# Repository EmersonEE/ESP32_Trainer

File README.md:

# ESP32 Trainer
Proyecto de Electrónica Aplicada 1 - **USAC**

# 📘 Temario del Proyecto

- 🔹 [Introducción](#-introducción)
- 🔹 [ESP32 Trainer](#-esp32-trainer)
- 🔹 [ESP32 Trainer Pinout](#esp32-trainer-pinout)
- 🔹 [Materiales](#-materiales)
- 🔹 [Diseño PCB - KiCad](#-diseño-pcb---kicad)
- 🔹 [Proyectos Demostrativos](#-proyectos-demostrativos)
<!-- - 🎥 [Video de Funcionamiento](#video-de-funcionamiento) -->

---

## 🧩 Introducción

En el ámbito del diseño electrónico y el desarrollo de prototipos, existe una necesidad creciente de contar con herramientas integradas que simplifiquen el proceso de aprendizaje, experimentación y construcción de soluciones funcionales. Las placas de desarrollo convencionales suelen requerir múltiples módulos adicionales para realizar proyectos completos, lo que incrementa la complejidad, los costos y el tiempo de implementación.

Este proyecto propone el diseño y fabricación de una **placa entrenadora basada en el [ESP32-WROOM-32](https://www.espressif.com/sites/default/files/documentation/esp32-wroom-32_datasheet_en.pdf)**, orientada a estudiantes, makers y profesionales. Su objetivo es integrar en una sola plataforma los elementos esenciales para trabajar con entradas/salidas digitales y analógicas, comunicación serial, control de cargas de alto voltaje, y más.

Entre sus características destacan:

- 🔘 Botones, LEDs y potenciómetros integrados para pruebas rápidas.
- ⚡ Control de cargas de 110V/220V mediante relés.
- 🔌 Interfaces UART, I2C y SPI disponibles desde headers.
- 📦 Diseño compacto y profesional en PCB de doble capa.

Con esta solución, se busca facilitar el desarrollo de proyectos de electrónica y automatización, reduciendo la necesidad de hardware adicional y mejorando la experiencia de aprendizaje.

[🔙 Volver al Temario](#-temario-del-proyecto)

## 🔌 ESP32 Trainer

[🔙 Volver al Temario](#-temario-del-proyecto)

## ESP32 Trainer Pinout

[Ver en PDF](pinout_esp32.pdf)

[🔙 Volver al Temario](#-temario-del-proyecto)

## 🧰 Materiales  

En esta sección se detallan todos los componentes electrónicos utilizados para el ensamblaje de la placa entrenadora basada en el ESP32-WROOM-32. La tabla incluye el identificador de cada componente, la cantidad necesaria, su valor o referencia, y el modelo de huella utilizado en el diseño PCB con KiCad.

<details><summary><b>Lista de Materiales  - BOM</b></summary>

| 🧾 Componente | 🔢 Cantidad | 💡 Valor       | 📐 Huella (KiCad)                                          |
|--------------|-------------|----------------|-------------------------------------------------------------|
| BZ1          | 1           | Buzzer         | Buzzer_12x9.5RM7.6                                          |
| C1, C2       | 2           | 22pF           | C_1206_3216Metric_Pad1.33x1.80mm_HandSolder                 |
| C10, C12     | 2           | 100uF          | CP_Elec_5x5.4                                               |
| C11, C13, C5, C6, C9 | 5   | 100nF          | C_1206_3216Metric_Pad1.33x1.80mm_HandSolder                 |
| C14–C16, C3–C4, C7–C8 | 7 | 0.1uF          | C_1206_3216Metric_Pad1.33x1.80mm_HandSolder                 |
| D1, D10, D7  | 3           | LED Verde      | LED_1210_3225Metric_Pad1.42x2.65mm_HandSolder               |
| D11, D13, D9 | 3           | SS24           | D_SMA                                                       |
| D12, D3, D8  | 3           | LED Azul       | LED_1210_3225Metric_Pad1.42x2.65mm_HandSolder               |
| D14–D16      | 3           | WS2812B        | LED_WS2812B_PLCC4_5.0x5.0mm_P3.2mm                          |
| D2           | 1           | LED Amarillo   | LED_1210_3225Metric_Pad1.42x2.65mm_HandSolder               |
| D4–D6        | 3           | LED Rojo       | LED_1210_3225Metric_Pad1.42x2.65mm_HandSolder               |
| J1           | 1           | USB B          | USB_B_Lumberg_2411_02_Horizontal                            |
| J10, J9      | 2           | —              | PinHeader_1x03_P2.54mm_Vertical                             |
| J2           | 1           | GPIO           | PinHeader_2x04_P2.54mm_Vertical                             |
| J3           | 1           | OLED           | PinSocket_1x04_P2.54mm_Vertical                             |
| J4           | 1           | —              | PinHeader_1x04_P2.54mm_Vertical                             |
| J5           | 1           | —              | PinHeader_2x03_P2.54mm_Vertical                             |
| J6–J8        | 3           | —              | TerminalBlock_Phoenix_MKDS-1,5-3-5.08_1x03_P5.08mm_Horizontal |
| K1–K3        | 3           | —              | Relay_SPDT_SANYOU_SRD_Series_Form_C                         |
| Q1–Q6        | 6           | MMBT3904       | SOT-23                                                      |
| R1, R2, R7, R9, R11, R12 | 6 | 10K         | R_1206_3216Metric_Pad1.30x1.75mm_HandSolder                 |
| R8, R10, R13–R16, R19–R21, R24 | 10 | 470   | R_1206_3216Metric_Pad1.30x1.75mm_HandSolder                 |
| R17, R22–R23, R25 | 4      | 2.2K           | R_1206_3216Metric_Pad1.30x1.75mm_HandSolder                 |
| R18          | 1           | 4.7K           | R_1206_3216Metric_Pad1.30x1.75mm_HandSolder                 |
| R26          | 1           | 220            | R_1206_3216Metric_Pad1.30x1.75mm_HandSolder                 |
| R3, R4       | 2           | 2K             | R_1206_3216Metric_Pad1.30x1.75mm_HandSolder                 |
| R5, R6       | 2           | 1K             | R_1206_3216Metric_Pad1.30x1.75mm_HandSolder                 |
| RV1, RV2     | 2           | 100K Pot       | Potentiometer_Bourns_3296W_Vertical                         |
| SW1, SW2     | 2           | —              | SW_Tactile_SPST_NO_Straight_CK_PTS636Sx25SMTRLFS            |
| SW3, SW4     | 2           | —              | SW_PUSH_6mm                                                 |
| U1           | 1           | ESP32-WROOM-32 | ESP32-WROOM-32                                              |
| U2           | 1           | CH340G         | SOIC-16_3.9x9.9mm_P1.27mm                                   |
| U3           | 1           | AMS1117-3.3    | SOT-223-3_TabPin2                                           |
| U4–U6        | 3           | PC817          | DIP-4_W7.62mm                                               |
| Y1           | 1           | 12MHz          | Crystal_HC49-4H_Vertical                                    |
</details>

[🔙 Volver al Temario](#-temario-del-proyecto)

## 🖨️ Diseño PCB - KiCad

 [KiCad](https://www.kicad.org/) se utilizó para el diseño de la placa entrenadora basada en el ESP32-WROOM-32, permitiendo crear el esquemático del circuito, asignar huellas adecuadas a los componentes y generar el diseño del PCB en múltiples capas. Gracias a sus herramientas de visualización y comprobación de reglas, fue posible optimizar el diseño para su posterior fabricación con alta precisión.

<details><summary><b>📏 Esquemático KiCad</b></summary>

Esquemático diseñado en Kicad, se puede visualizar de forma completa en este enlace [Esquemático](Schematic.pdf)
<div align="center" >
  <p style="text-align:center;"><strong>Power Supply</strong></p>
  
</div>

<div align="center" >
  <p style="text-align:center;"><strong>USB To TTL</strong></p>
  
</div>

<div align="center" >
  <p style="text-align:center;"><strong>Boot Settings</strong></p>
  
</div>

<div align="center" >
  <p style="text-align:center;"><strong>INPUT - OUTPUT Digital</strong></p>
  
</div>

<div align="center" >
  <p style="text-align:center;"><strong>ESP32-WROOM</strong></p>
  
</div>

<div align="center" >
  <p style="text-align:center;"><strong>Analog INPUT</strong></p>
  
</div>

<div align="center" >
  <p style="text-align:center;"><strong>LED WS2812B</strong></p>
  
</div>

<div align="center" >
  <p style="text-align:center;"><strong>Buzzer</strong></p>
  
</div>

<div align="center" >
  <p style="text-align:center;"><strong>Jumper Selector</strong></p>
  
</div>

<div align="center" >
  <p style="text-align:center;"><strong>GPIO - UART</strong></p>
  
</div>

<div align="center" >
  <p style="text-align:center;"><strong>OLED I2C</strong></p>
  
</div>

<div align="center" >
  <p style="text-align:center;"><strong>Rele</strong></p>
  
</div>

</details>

<details><summary><b>🔌 Diseño del PCB </b></summary>

Diseño de la PCB en dos caras, se puede descargar los archivos para su modificación o su estudio en aca [Descargar archivos del  PCB](https://github.com/EmersonEE/ESP32_Trainer/releases/tag/untagged-a26e2b24809520548798)

<div align="center" >
  <p style="text-align:center;"><strong>Diseño 3D</strong></p>
  
</div>

<div align="center" >
  <p style="text-align:center;"><strong>Capa BUTTON</strong></p>
  
</div>

<div align="center" >
  <p style="text-align:center;"><strong>Capa TOP</strong></p>
  
</div>

<div align="center" >
  <p style="text-align:center;"><strong>Serigrafía</strong></p>
  
</div>

</details>

<details><summary><b>🖥️ Introducción a KiCad</b></summary>

KiCad es una suite de software libre para el diseño de circuitos electrónicos y la creación de placas de circuito impreso (PCB). Desarrollado originalmente por Jean-Pierre Charras y mantenido actualmente por la comunidad y la Fundación KiCad, es una herramienta poderosa y versátil que compite con soluciones comerciales en la industria electrónica.

[KiCad](https://www.kicad.org/) permite a los diseñadores electrónicos trabajar de forma integral en todo el flujo de desarrollo de hardware, desde la creación de esquemáticos eléctricos hasta la generación de archivos Gerber listos para fabricación. Entre sus principales características destacan:

✏️ Editor de esquemáticos intuitivo, con bibliotecas extensas de componentes.

🧩 Gestor de huellas (footprints) que vincula componentes con sus representaciones físicas en el PCB.

🖨️ Editor de PCB con reglas de diseño personalizables y soporte para múltiples capas.

📷 Visualizador 3D para inspeccionar el diseño de la placa antes de fabricarla.

🔁 Integración con herramientas externas para simulación eléctrica (SPICE) o gestión de proyectos.

Al ser de código abierto y multiplataforma (disponible en Windows, Linux y macOS), KiCad es una opción ideal tanto para estudiantes, makers, como para profesionales del diseño electrónico.

## 📺 Tutoriales KiCad

### Guía para el uso de KiCad #1

### Guía para el uso de KiCad #2

### Guía para el uso de KiCad #3

</details>

[🔙 Volver al Temario](#-temario-del-proyecto)

## 🧪 Proyectos Demostrativos

Con el objetivo de validar y demostrar la versatilidad de la placa entrenadora basada en el ESP32-WROOM-32, se desarrollaron cinco proyectos demostrativos que abarcan desde aplicaciones básicas hasta implementaciones más avanzadas. Estos proyectos fueron diseñados para cubrir distintos niveles de complejidad, permitiendo así ilustrar de manera progresiva el potencial de la placa tanto en el ámbito educativo como en entornos de prototipado profesional.

Cada proyecto está enfocado en destacar una o varias funcionalidades integradas de la placa, como el uso de salidas digitales con visualización por LEDs, entradas analógicas controladas por potenciómetros, manejo de salidas de alto voltaje mediante relés, así como el uso de interfaces de comunicación como UART, I2C.

<details><summary><b>🤖 💡 Proyecto 1 </b></summary>

## Proyecto: Control de Intensidad de LED con Clases Personalizadas

Este proyecto implementa un sistema modular en Arduino para el **control de un LED** utilizando clases personalizadas en C++.

### Características principales:

- **Clase `LED`**: Permite controlar un LED conectado a un pin digital o PWM. Soporta funciones como encendido, apagado, parpadeo y control de brillo mediante modulación por ancho de pulso (PWM).
- **Clase `PWM`**: Facilita la lectura de entradas analógicas y entrega los valores en diferentes formatos: raw, mapeado (0-255) y en voltios.
- En la función `setup()`, se configura un LED en el pin 2 en modo PWM.
- En el `loop()`, la intensidad del LED se ajusta dinámicamente según la lectura analógica del pin 32.

Este proyecto demuestra cómo estructurar el código de forma reutilizable y orientada a objetos para controlar hardware de forma más eficiente.

🔗 [Ver código del Proyecto 1](/Codigos%20Proyectos/Proyecto_1/)

</details>

<details><summary><b>🤖 💡 Proyecto 2 </b></summary>

## Proyecto: Detección de Movimiento y Control Remoto vía Telegram

Este proyecto implementa un sistema de monitoreo basado en **ESP32** que permite detectar movimiento mediante un sensor **PIR** y enviar notificaciones en tiempo real a un usuario específico a través de un bot de **Telegram**.

### Características principales:

- **Detección de movimiento**: El sensor PIR detecta presencia o movimiento en el entorno.
- **Notificación instantánea**: Cuando se detecta movimiento, el ESP32 envía un mensaje automáticamente al usuario mediante Telegram.
- **Control remoto**: El usuario puede encender o apagar un **LED** conectado al ESP32 enviando comandos personalizados al bot.
- **Interacción segura y directa**: Solo el usuario autorizado puede comunicarse con el bot para recibir alertas o enviar comandos.
- **Aplicación práctica**: Ideal para sistemas de vigilancia, alarmas domésticas o control remoto básico mediante mensajería.

🔗 [Ver código del Proyecto 2](/Codigos%20Proyectos/Proyecto_2/)

</details>

<details><summary><b>🤖 💡 Proyecto 3 </b></summary>

## Proyecto: Control de Focos con ESP32 y ESP RainMaker

Este proyecto utiliza un ESP32 para controlar tres focos a través de la plataforma **ESP RainMaker**, permitiendo el encendido y apagado mediante comandos de voz e integración con asistentes virtuales.

### Características principales:

- **Control inteligente**: Tres relés controlan los focos conectados a los pines **25**, **2** y **14**.
- **Dispositivos virtuales**: Se crean tres dispositivos en la nube:
  - `Foco Sala`
  - `Foco Comedor`
  - `Foco Cuarto`
- **Comandos de voz**: Compatible con asistentes virtuales mediante ESP RainMaker.
- **Aprovisionamiento BLE**: Permite la configuración inicial de red Wi-Fi mediante Bluetooth.
- **Callback personalizado**: Al recibir una orden desde RainMaker, el estado del relé correspondiente se actualiza.
- **Actualización OTA**: Soporte para actualizaciones de firmware a distancia.
- **Servicios integrados**:
  - Zona horaria
  - Programación de tareas
- **Indicadores y botones**:
  - LED indica conexión Wi-Fi activa.
  - Botón en el pin **0** permite:
    - Restablecer Wi-Fi (pulsación breve)
    - Restablecer de fábrica (pulsación prolongada)

Este proyecto es ideal para aplicaciones de automatización del hogar, demostrando la capacidad de la placa para integrarse con servicios en la nube y control por voz.

🔗 [Ver código del Proyecto 3](/Codigos%20Proyectos/Proyecto_3/)

</details>

<details><summary><b>🤖 💡 Proyecto 4 </b></summary>

## Proyecto: Controlador Web para LED RGB con ESP32

Gracias al módulo WiFi integrado del **ESP32**, es posible crear un controlador web altamente funcional para un **LED RGB**, eliminando la necesidad de ingresar manualmente valores RGB cada vez que se desea cambiar el color.

En lugar de eso, este proyecto propone una **interfaz web atractiva e interactiva**, que permite seleccionar colores de forma visual e intuitiva. Para ello, se utiliza la biblioteca **iro.js**, un potente selector de color en JavaScript que ofrece una experiencia de usuario dinámica y visualmente agradable.

La comunicación entre la interfaz web y el ESP32 se realiza mediante **WebSockets**, lo que permite actualizar el color en tiempo real sin necesidad de recargar la página. El **ESP32 actúa como servidor Web**, sirviendo la interfaz HTML y gestionando el servidor WebSocket para recibir los datos del color seleccionado.

Este enfoque proporciona un sistema eficiente, moderno y fácil de usar para controlar luces RGB a través de cualquier dispositivo con acceso a un navegador web.

[Manera de subir la carpeta Data al ESP32](https://randomnerdtutorials.com/esp32-vs-code-platformio-spiffs/)

🔗 [Ver código del Proyecto 4](/Codigos%20Proyectos/Proyecto_4/)

</details>

<details><summary><b>🤖 💡 Proyecto 5 </b></summary>

## Proyecto: Alerta de Proximidad con Sensor Ultrasónico, Pantalla OLED y Buzzer

Este proyecto utiliza un **sensor ultrasónico**, una **pantalla OLED SSD1306** y un **buzzer** para crear un sistema de alerta de proximidad.

### Funcionamiento:

- El **sensor ultrasónico** mide constantemente la distancia a un objeto frente a él.
- La **pantalla OLED** muestra en tiempo real la distancia detectada en centímetros.
- Cuando un objeto se acerca a una **distancia mínima predefinida**, el **buzzer** se activa como señal de advertencia sonora.
- Si el objeto se aleja nuevamente más allá del umbral, el buzzer se desactiva automáticamente.

Este sistema es útil como sistema de asistencia para estacionamiento, detección de intrusos, monitoreo de espacios reducidos, entre otros usos prácticos que requieren una alerta ante la cercanía de objetos.

🔗 [Ver código del Proyecto 5](/Codigos%20Proyectos/Proyecto_5/)

</details>

[🔙 Volver al Temario](#-temario-del-proyecto)

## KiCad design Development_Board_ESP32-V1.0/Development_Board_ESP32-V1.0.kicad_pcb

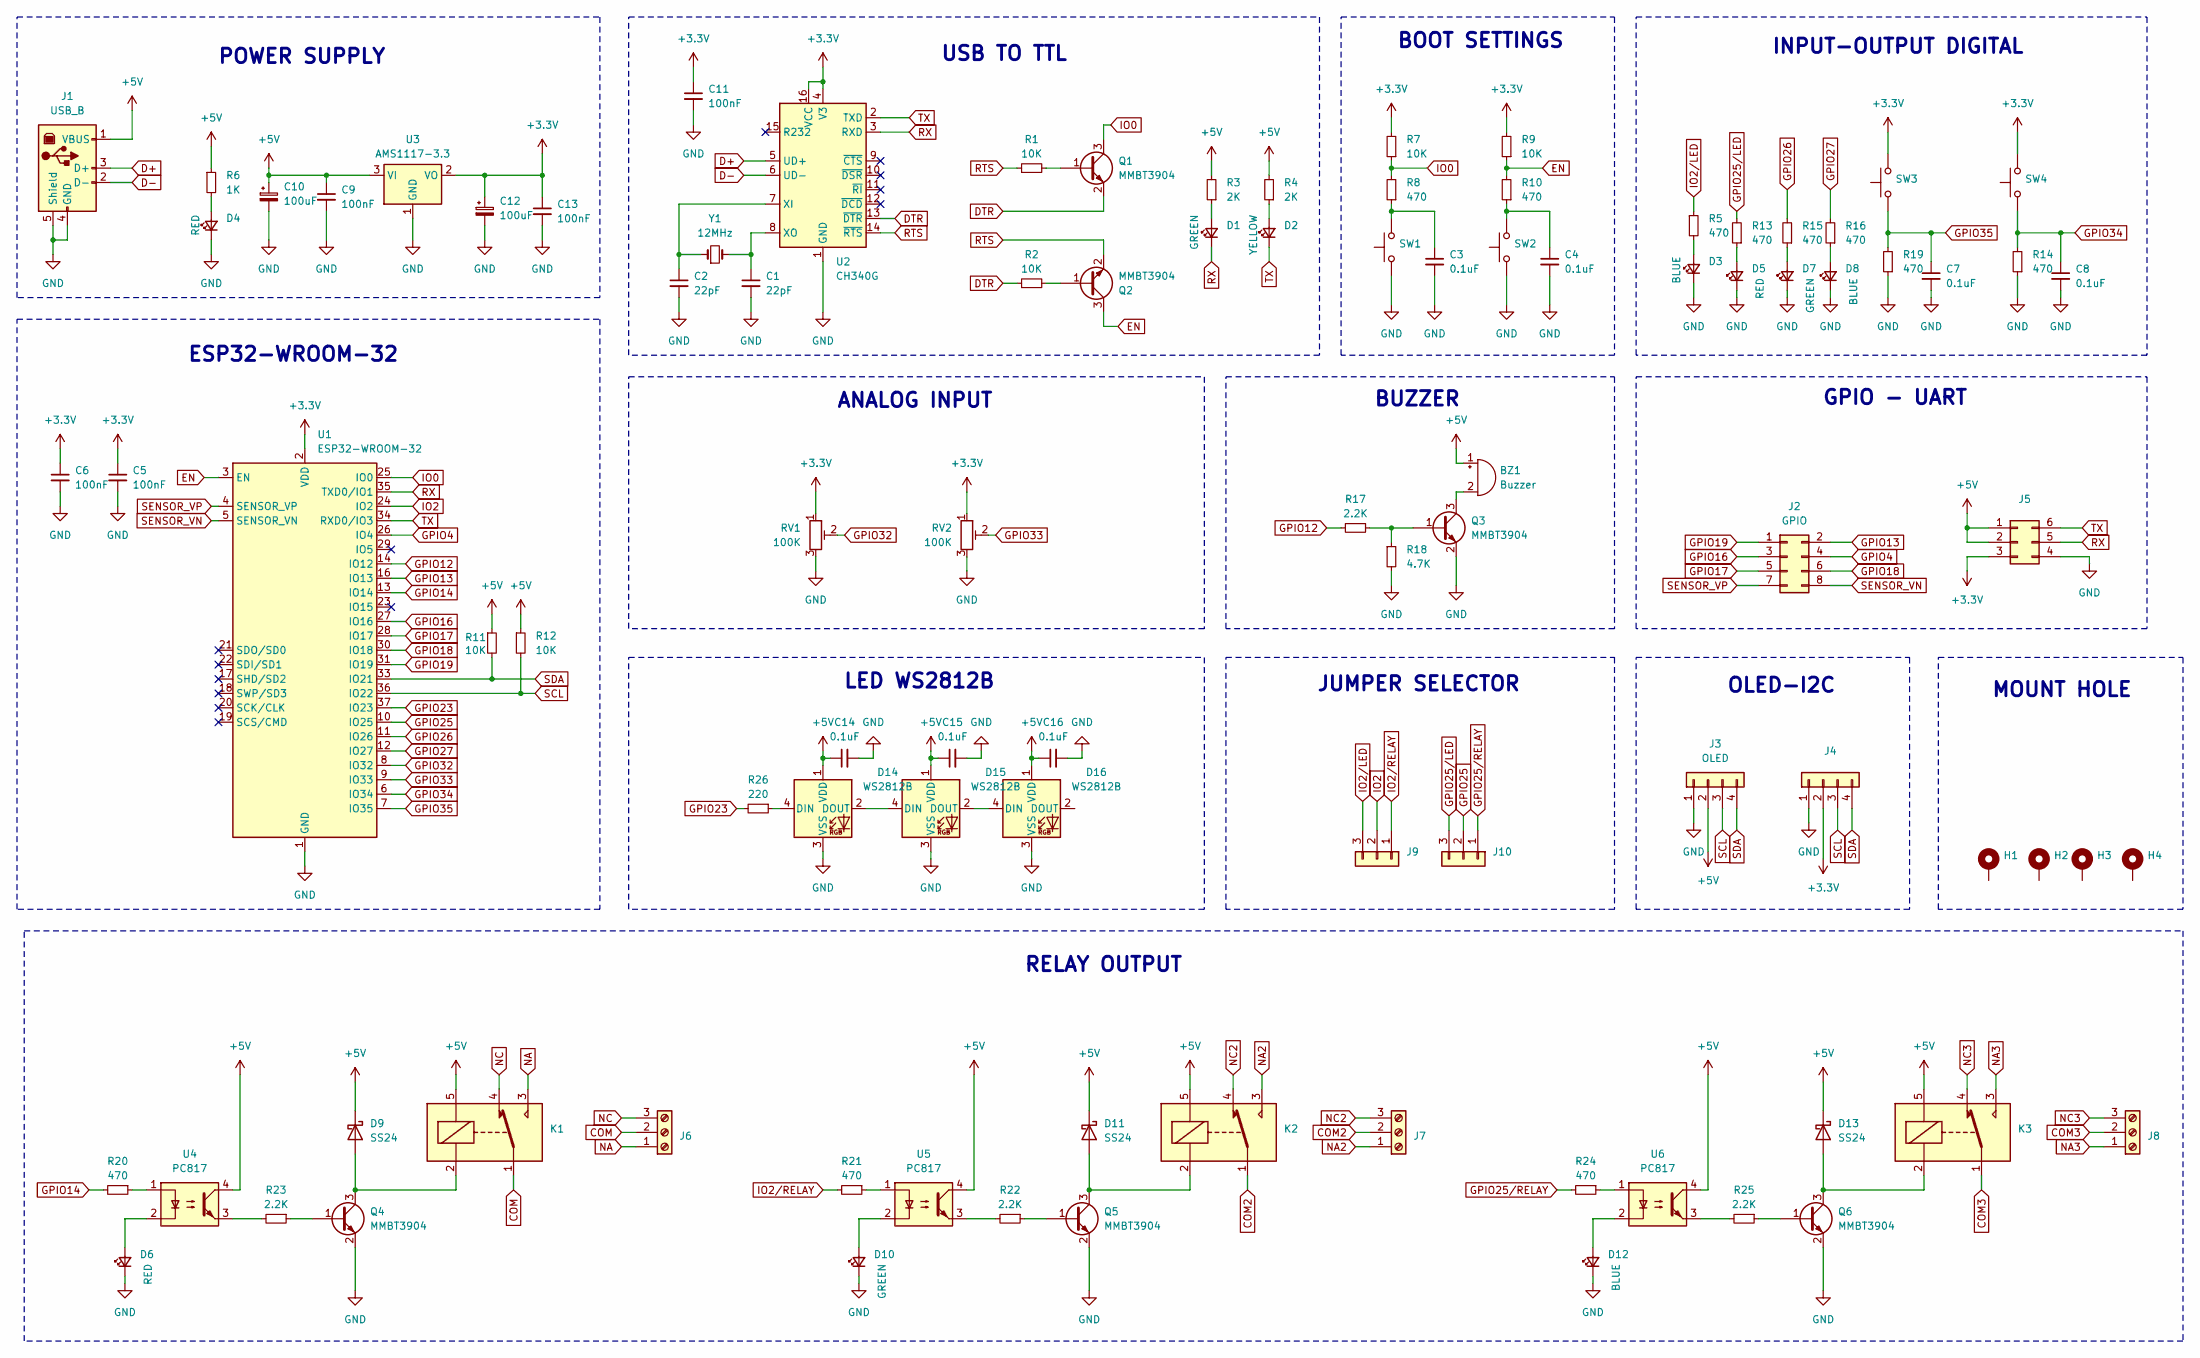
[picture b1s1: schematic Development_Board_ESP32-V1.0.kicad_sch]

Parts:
BZ1: Buzzer; Buzzer_12x9.5RM7.6
C1, C2: 22pF; C_1206_3216Metric_Pad1.33x1.80mm_HandSolder
C3, C4, C7, C8, C14, C15, C16: 0.1uF; C_1206_3216Metric_Pad1.33x1.80mm_HandSolder
C5, C6, C9, C11, C13: 100nF; C_1206_3216Metric_Pad1.33x1.80mm_HandSolder
C10, C12: 100uF; CP_Elec_5x5.4
D1, D7, D10: GREEN; LED_1210_3225Metric_Pad1.42x2.65mm_HandSolder
D2: YELLOW; LED_1210_3225Metric_Pad1.42x2.65mm_HandSolder
D3, D8, D12: BLUE; LED_1210_3225Metric_Pad1.42x2.65mm_HandSolder
D4, D5, D6: RED; LED_1210_3225Metric_Pad1.42x2.65mm_HandSolder
D9, D11, D13: SS24; D_SMA
D14, D15, D16: WS2812B; LED_WS2812B_PLCC4_5.0x5.0mm_P3.2mm
H1, H2, H3, H4: MountingHole_3.2mm_M3_Pad_Via
J1: USB_B; USB_B_Lumberg_2411_02_Horizontal
J2: GPIO; PinHeader_2x04_P2.54mm_Vertical
J3: OLED; PinSocket_1x04_P2.54mm_Vertical
J4: PinHeader_1x04_P2.54mm_Vertical
J5: PinHeader_2x03_P2.54mm_Vertical
J6, J7, J8: TerminalBlock_Phoenix_MKDS-1,5-3-5.08_1x03_P5.08mm_Horizont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
J9, J10: PinHeader_1x03_P2.54mm_Vertical
K1, K2, K3: Relay_SPDT_SANYOU_SRD_Series_Form_C
Q1, Q2, Q3, Q4, Q5, Q6: MMBT3904; SOT-23
R1, R2, R7, R9, R11, R12: 10K; R_1206_3216Metric_Pad1.30x1.75mm_HandSolder
R3, R4: 2K; R_1206_3216Metric_Pad1.30x1.75mm_HandSolder
R5, R8, R10, R13, R14, R15, R16, R19, R20, R21, R24: 470; R_1206_3216Metric_Pad1.30x1.75mm_HandSolder
R6: 1K; R_1206_3216Metric_Pad1.30x1.75mm_HandSolder
R17, R22, R23, R25: 2.2K; R_1206_3216Metric_Pad1.30x1.75mm_HandSolder
R18: 4.7K; R_1206_3216Metric_Pad1.30x1.75mm_HandSolder
R26: 220; R_1206_3216Metric_Pad1.30x1.75mm_HandSolder
RV1, RV2: 100K; Potentiometer_Bourns_3296W_Vertical
SW1, SW2: SW_Tactile_SPST_NO_Straight_CK_PTS636Sx25SMTRLFS
SW3, SW4: SW_PUSH_6mm
U1: ESP32-WROOM-32
U2: CH340G; SOIC-16_3.9x9.9mm_P1.27mm
U3: AMS1117-3.3; SOT-223-3_TabPin2
U4, U5, U6: PC817; DIP-4_W7.62mm
Y1: 12MHz; Crystal_HC49-4H_Vertical

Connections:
+3.3V: C5.1, C6.1, C11.1, C12.1, C13.1, J4.2, J5.3, R7.2, R9.2, RV1.1, RV2.1, SW3.2, SW4.2, U1.2 (VDD), U2.4 (V3), U2.16 (VCC), U3.2 (VO)
+5V: BZ1.1 (+), C9.1, C10.1, C14.1, C15.1, C16.1, D9.1 (K), D11.1 (K), D13.1 (K), D14.1 (VDD), D15.1 (VDD), D16.1 (VDD), J1.1 (VBUS), J3.2, J5.1, J5.2, K1.5, K2.5, K3.5, R3.2, R4.2, R6.1, R11.1, R12.1, U3.3 (VI), U4.4, U5.4, U6.4
COM: J6.2, K1.1
COM2: J7.2, K2.1
COM3: J8.2, K3.1
D+: J1.3 (D+), U2.5 (UD+)
D-: J1.2 (D-), U2.6 (UD-)
DTR: Q1.2 (E), R2.1, U2.13 (~DTR)
EN: Q2.3 (C), R9.1, R10.2, U1.3 (EN)
GND: C1.2, C2.2, C3.2, C4.2, C5.2, C6.2, C7.2, C8.2, C9.2, C10.2, C11.2, C12.2, C13.2, C14.2, C15.2, C16.2, D3.1 (K), D4.1 (K), D5.1 (K), D6.1 (K), D7.1 (K), D8.1 (K), D10.1 (K), D12.1 (K), D14.3 (VSS), D15.3 (VSS), D16.3 (VSS), J1.4 (GND), J1.5 (Shield), J3.1, J4.1, J5.4, Q3.2 (E), Q4.2 (E), Q5.2 (E), Q6.2 (E), R14.1, R18.2, R19.1, RV1.3, RV2.3, SW1.1, SW2.1, U1.1 (GND), U1.15 (GND), U1.38 (GND), U1.39 (GND), U2.1 (GND), U3.1 (GND)
GPIO4: J2.4, U1.26 (IO4)
GPIO12: R17.2, U1.14 (IO12)
GPIO13: J2.2, U1.16 (IO13)
GPIO14: R20.2, U1.13 (IO14)
GPIO16: J2.3, U1.27 (IO16)
GPIO17: J2.5, U1.28 (IO17)
GPIO18: J2.6, U1.30 (IO18)
GPIO19: J2.1, U1.31 (IO19)
GPIO23: R26.2, U1.37 (IO23)
GPIO25: J10.2, U1.10 (IO25)
GPIO25/LED: J10.3, R13.2
GPIO25/RELAY: J10.1, R24.2
GPIO26: R15.2, U1.11 (IO26)
GPIO27: R16.2, U1.12 (IO27)
GPIO32: RV1.2, U1.8 (IO32)
GPIO33: RV2.2, U1.9 (IO33)
GPIO34: C8.1, R14.2, SW4.1, U1.6 (IO34)
GPIO35: C7.1, R19.2, SW3.1, U1.7 (IO35)
IO0: Q1.3 (C), R7.1, R8.2, U1.25 (IO0)
IO2: J9.2, U1.24 (IO2)
IO2/LED: J9.3, R5.1
IO2/RELAY: J9.1, R21.2
NA: J6.1, K1.3
NA2: J7.1, K2.3
NA3: J8.1, K3.3
NC: J6.3, K1.4
NC2: J7.3, K2.4
NC3: J8.3, K3.4
unnamed: BZ1.2 (-), Q3.3 (C)
unnamed: C3.1, R8.1, SW1.2
unnamed: C4.1, R10.1, SW2.2
unnamed: D1.2 (A), R3.1
unnamed: D2.2 (A), R4.1
unnamed: D3.2 (A), R5.2
unnamed: D4.2 (A), R6.2
unnamed: D5.2 (A), R13.1
unnamed: D6.2 (A), U4.2
unnamed: D7.2 (A), R15.1
unnamed: D8.2 (A), R16.1
unnamed: D9.2 (A), K1.2, Q4.3 (C)
unnamed: D10.2 (A), U5.2
unnamed: D11.2 (A), K2.2, Q5.3 (C)
unnamed: D12.2 (A), U6.2
unnamed: D13.2 (A), K3.2, Q6.3 (C)
unnamed: D14.4 (DIN), R26.1
unnamed: D14.2 (DOUT), D15.4 (DIN)
unnamed: D15.2 (DOUT), D16.4 (DIN)
unnamed: Q1.1 (B), R1.2
unnamed: Q2.1 (B), R2.2
unnamed: Q3.1 (B), R17.1, R18.1
unnamed: Q4.1 (B), R23.1
unnamed: Q5.1 (B), R22.1
unnamed: Q6.1 (B), R25.1
unnamed: R20.1, U4.1
unnamed: R21.1, U5.1
unnamed: R22.2, U5.3
unnamed: R23.2, U4.3
unnamed: R24.1, U6.1
unnamed: R25.2, U6.3
unnamed: C2.1, U2.7 (XI), Y1.1
unnamed: C1.1, U2.8 (XO), Y1.2
RTS: Q2.2 (E), R1.1, U2.14 (~RTS)
RX: D1.1 (K), J5.5, U1.35 (TXD0/IO1), U2.3 (RXD)
SCL: J3.3, J4.3, R12.2, U1.36 (IO22)
SDA: J3.4, J4.4, R11.2, U1.33 (IO21)
SENSOR_VN: J2.8, U1.5 (SENSOR_VN)
SENSOR_VP: J2.7, U1.4 (SENSOR_VP)
TX: D2.1 (K), J5.6, U1.34 (RXD0/IO3), U2.2 (TXD)

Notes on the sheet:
ANALOG INPUT
BUZZER
ESP32-WROOM-32
POWER SUPPLY
LED WS2812B
MOUNT HOLE
INPUT-OUTPUT DIGITAL
BOOT SETTINGS
RELAY OUTPUT
JUMPER SELECTOR
GPIO - UART
OLED-I2C
USB TO TTL

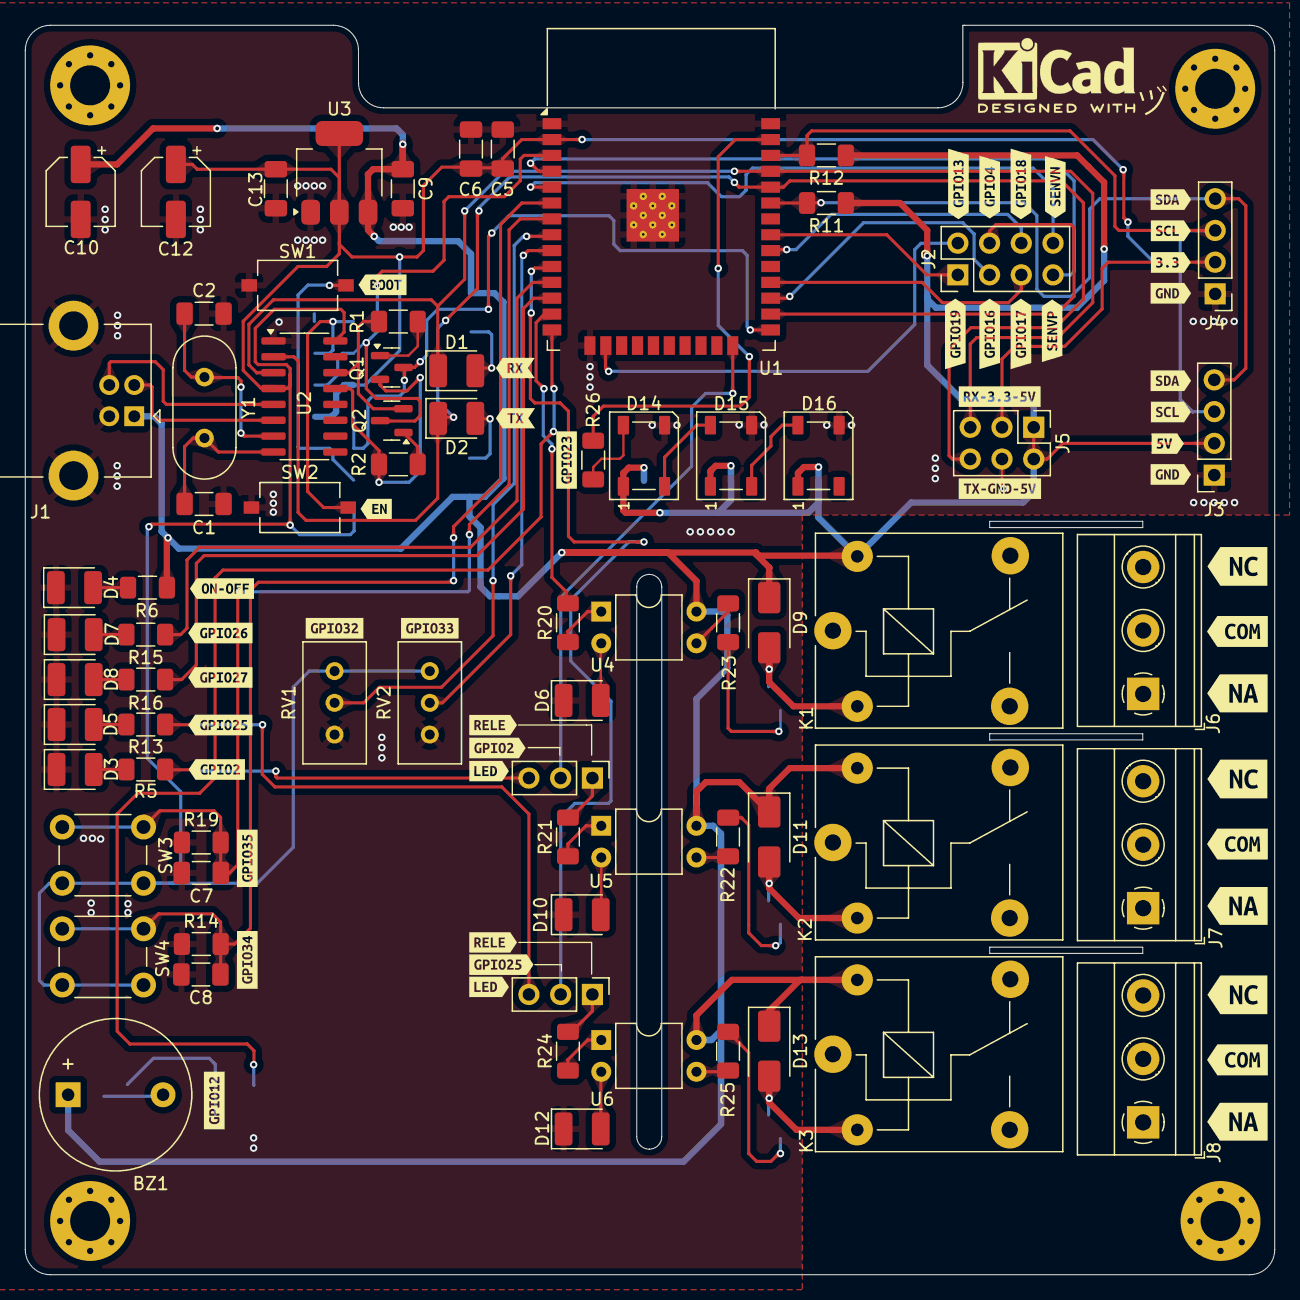
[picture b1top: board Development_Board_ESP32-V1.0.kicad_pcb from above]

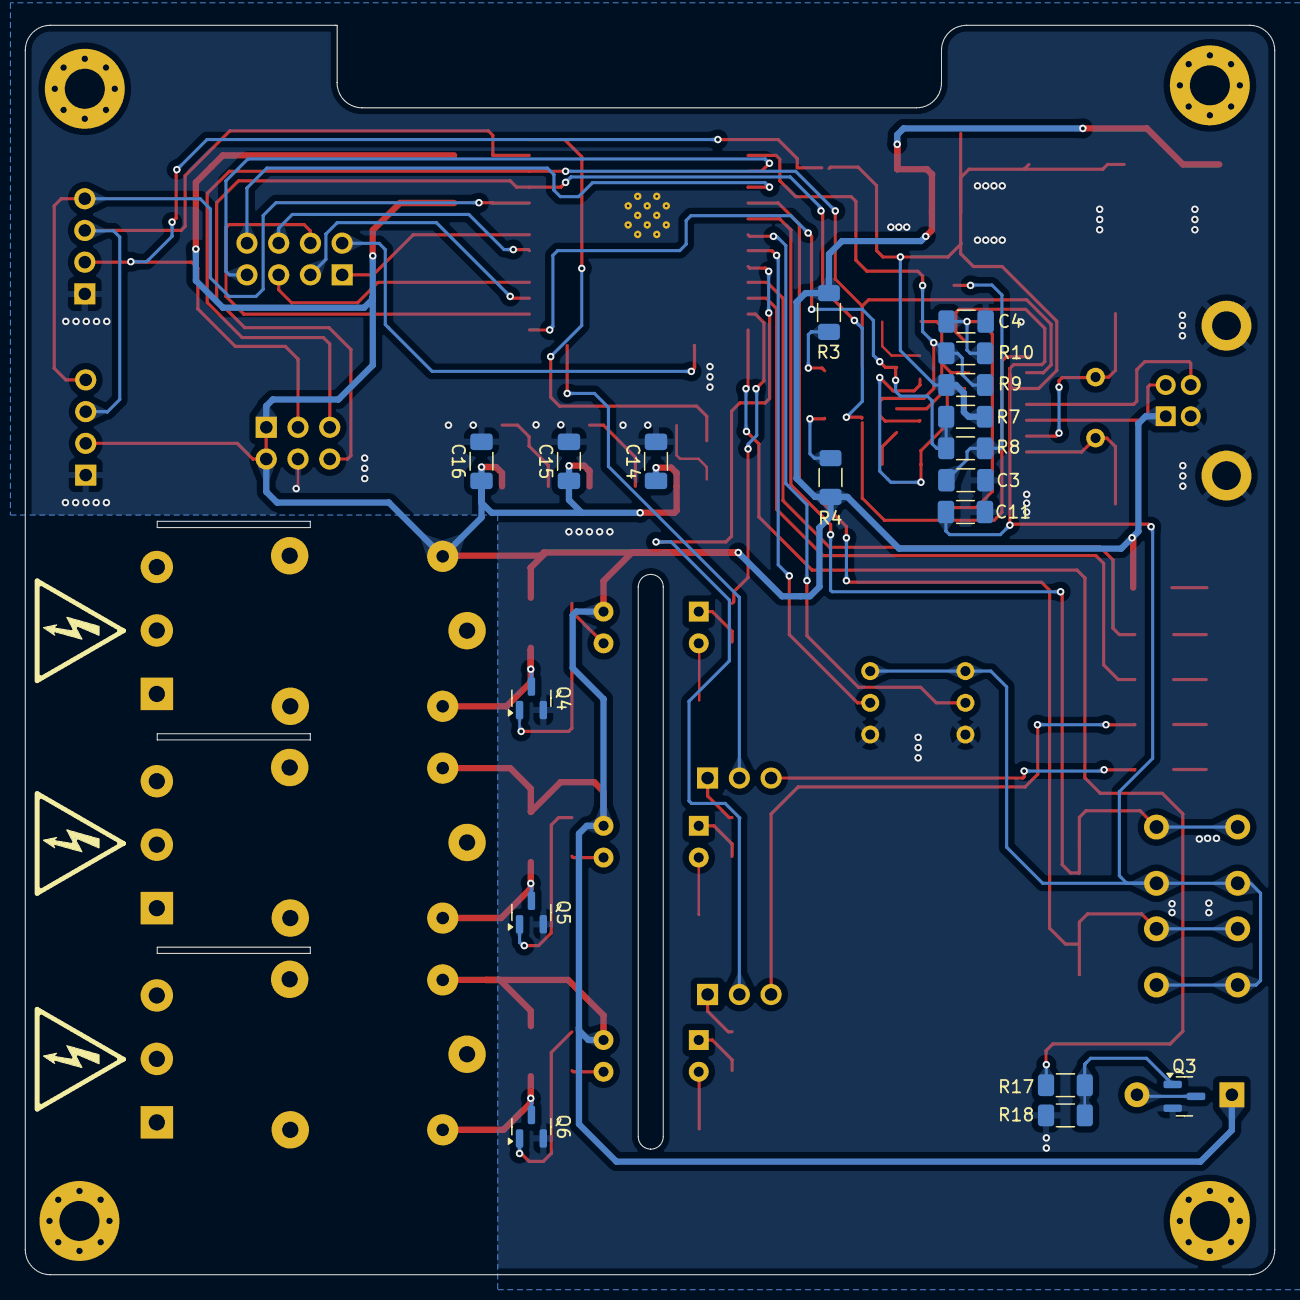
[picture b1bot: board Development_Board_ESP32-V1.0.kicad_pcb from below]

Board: 2 copper layers, 100.0 x 100.0 mm, 143 parts (18 on the bottom side), 78 nets.

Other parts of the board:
kibuzzard-67C7CC9C: G***; kibuzzard-67C7CC9C
kibuzzard-67C7CCC6: G***; kibuzzard-67C7CCC6
kibuzzard-67C7CCDB: G***; kibuzzard-67C7CCDB
kibuzzard-67C7CD00: G***; kibuzzard-67C7CD00
kibuzzard-67C7CD0D: G***; kibuzzard-67C7CD0D
kibuzzard-67C7CD05: G***; kibuzzard-67C7CD05
kibuzzard-67C7CEE3, kibuzzard-67C7CEE3#2: G***; kibuzzard-67C7CEE3
kibuzzard-67C7CEF2, kibuzzard-67C7CEF2#2: G***; kibuzzard-67C7CEF2
kibuzzard-67C7CF27, kibuzzard-67C7CF27#2: G***; kibuzzard-67C7CF27
kibuzzard-67C7CF34: G***; kibuzzard-67C7CF34
kibuzzard-67C7CF78: G***; kibuzzard-67C7CF78
kibuzzard-67C7CFC3, kibuzzard-67C7CFC3#2: G***; kibuzzard-67C7CFC3
kibuzzard-67C7D0D9, kibuzzard-67C7D0D9#2, kibuzzard-67C7D0D9#3: G***; kibuzzard-67C7D0D9
kibuzzard-67C7D0EE, kibuzzard-67C7D0EE#2, kibuzzard-67C7D0EE#3: G***; kibuzzard-67C7D0EE
kibuzzard-67C7D02E, kibuzzard-67C7D02E#2: G***; kibuzzard-67C7D02E
kibuzzard-67C7D15A: G***; kibuzzard-67C7D15A
kibuzzard-67C7D26A: G***; kibuzzard-67C7D26A
kibuzzard-67C7D134: G***; kibuzzard-67C7D134
kibuzzard-67C7D148: G***; kibuzzard-67C7D148
kibuzzard-67C7D258: G***; kibuzzard-67C7D258
kibuzzard-67C8441C: G***; kibuzzard-67C8441C
kibuzzard-67C8442B: G***; kibuzzard-67C8442B
kibuzzard-67C84437: G***; kibuzzard-67C84437
kibuzzard-67C84440: G***; kibuzzard-67C84440
kibuzzard-67CB0A01: G***; kibuzzard-67CB0A01
kibuzzard-67CB0A75: G***; kibuzzard-67CB0A75
kibuzzard-67CB0A81: G***; kibuzzard-67CB0A81
kibuzzard-67CB0AA4: G***; kibuzzard-67CB0AA4
kibuzzard-67CB0AB6: G***; kibuzzard-67CB0AB6
kibuzzard-67CB0AEE: G***; kibuzzard-67CB0AEE
kibuzzard-67CB08BA: G***; kibuzzard-67CB08BA
kibuzzard-67CB08E7: G***; kibuzzard-67CB08E7
kibuzzard-67CB21E1: G***; kibuzzard-67CB21E1
kibuzzard-67CB32EA: G***; kibuzzard-67CB32EA
kibuzzard-67CB089A: G***; kibuzzard-67CB089A
kibuzzard-67CB0885: G***; kibuzzard-67CB0885
kibuzzard-67CB0907: G***; kibuzzard-67CB0907
kibuzzard-67CB0943: G***; kibuzzard-67CB0943
kibuzzard-67CB3300: G***; kibuzzard-67CB3300

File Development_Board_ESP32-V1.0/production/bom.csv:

Designator,Footprint,Quantity,Value,LCSC Part #
BZ1,Buzzer_12x9.5RM7.6,1,Buzzer,
"C1, C2",1206,2,22pF,
"C10, C12",CP_Elec_5x5.4,2,100uF,
"C11, C13, C5, C6, C9",1206,5,100nF,
"C14, C15, C16, C3, C4, C7, C8",1206,7,0.1uF,
"D1, D10, D7",1210,3,GREEN,
"D11, D13, D9",D_SMA,3,SS24,
"D12, D3, D8",1210,3,BLUE,
"D14, D15, D16",LED_WS2812B_PLCC4_5.0x5.0mm_P3.2mm,3,WS2812B,
D2,1210,1,YELLOW,
"D4, D5, D6",1210,3,RED,
J1,USB_B_Lumberg_2411_02_Horizontal,1,USB_B,
"J10, J9",PinHeader_1x03_P2.54mm_Vertical,2,~,
J2,PinHeader_2x04_P2.54mm_Vertical,1,GPIO,
J3,PinSocket_1x04_P2.54mm_Vertical,1,OLED,
J4,PinHeader_1x04_P2.54mm_Vertical,1,~,
J5,PinHeader_2x03_P2.54mm_Vertical,1,~,
"J6, J7, J8","TerminalBlock_Phoenix_MKDS-1,5-3-5.08_1x03_P5.08mm_Horizontal",3,~,
"K1, K2, K3",Relay_SPDT_SANYOU_SRD_Series_Form_C,3,~,
"Q1, Q2, Q3, Q4, Q5, Q6",SOT-23,6,MMBT3904,
"R1, R11, R12, R2, R7, R9",1206,6,10K,
"R10, R13, R14, R15, R16, R19, R20, R21, R24, R5, R8",1206,11,470,
"R17, R22, R23, R25",1206,4,2.2K,
R18,1206,1,4.7K,
R26,1206,1,220,
"R3, R4",1206,2,2K,
R6,1206,1,1K,
"RV1, RV2",Potentiometer_Bourns_3296W_Vertical,2,100K,
"SW1, SW2",SW_Tactile_SPST_NO_Straight_CK_PTS636Sx25SMTRLFS,2,~,
"SW3, SW4",SW_PUSH_6mm,2,~,
U1,ESP32-WROOM-32,1,ESP32-WROOM-32,
U2,SOIC-16_3.9x9.9mm_P1.27mm,1,CH340G,
U3,SOT-223-3_TabPin2,1,AMS1117-3.3,
"U4, U5, U6",DIP-4_W7.62mm,3,PC817,
Y1,Crystal_HC49-4H_Vertical,1,12MHz,

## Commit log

2025-03-18 Iniciando Proyecto
2025-03-18 Agregando Titulo
2025-03-18 Agregando Carpeta Codigos
2025-03-18 Agregando Proyecto KiCad
2025-03-21 Librerias Blink
2025-03-22 Librerias Botones
2025-03-23 Libreria PWM
2025-04-13 Haciendo las cosas bien XD
2025-04-14 Proyecto 1 Terminado
2025-04-15 Proyecto 3 Terminado
2025-04-19 Subiendo todo por si cambio
2025-04-29 Script Rainbo
2025-04-29 Agregando el Menu
2025-04-29 Arreglando el Temario
2025-04-29 Agregando Imagenes
2025-04-29 Subiendo Intro y Frames
2025-04-29 Subiendo Frames
2025-04-29 Arreglando los frames
2025-04-30 Arreglando los frames2
2025-04-30 Agregando ultimas imagenes del pcb
2025-04-30 Agregando el PCB - Esquematico
2025-04-30 Centrando Imagenes
2025-05-01 Decripcion 3 proyectos
2025-05-01 Decripcion 3 proyectos 1.0
2025-05-01 Agregando proyecto 4
2025-05-02 Agregando proyecto 5
2025-05-02 Agregando descripcion proyecto 4y 5
2025-05-12 Pinout
2025-05-17 Proyecto Terminado
2025-08-04 Arreglando Voltaje en esquematico
